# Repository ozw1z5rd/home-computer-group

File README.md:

# Home-Computer-Group

* ARM_ASM contains assembler programs you can run on Raspberry PI / PICO PI
* The C64 folder contains the source code as shown in the Home Computer Group e-magazine.
* KiCAD folder contains hardware projects for KiCAD
* Logicsim and LogiSimEvoluation are loaded with the circuits as shown in the Home Computer Group e-magazine.

Join us [Facebook group](https://fb.com/groups/home.computer) 

Visit us [Home Computer Group Website](https://homecomputer.group) 

Have fun with your Home Computer!

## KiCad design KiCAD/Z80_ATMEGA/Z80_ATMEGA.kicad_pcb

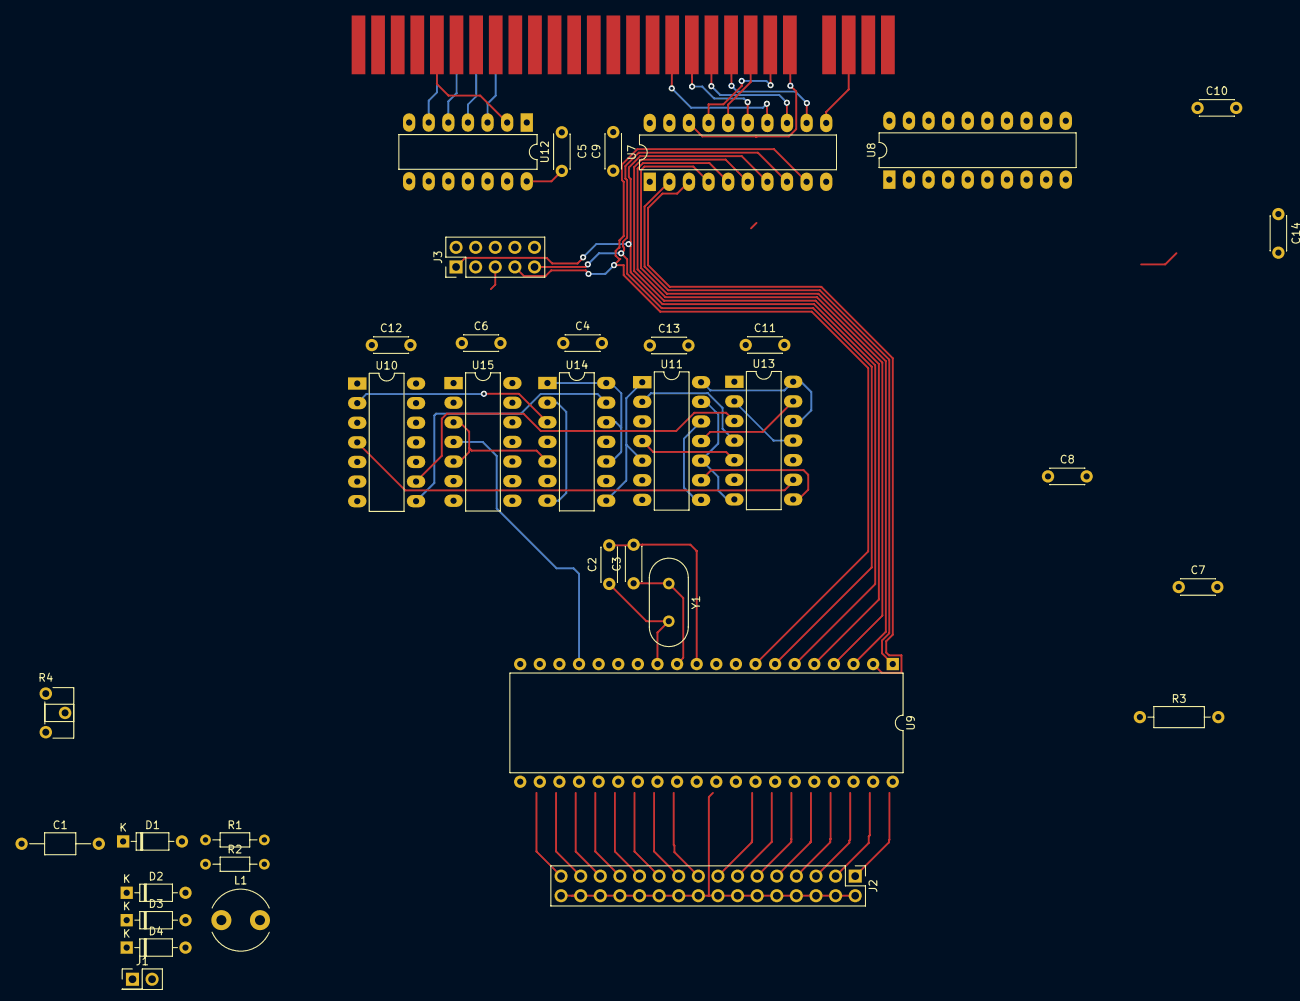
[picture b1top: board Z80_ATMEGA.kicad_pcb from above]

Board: 2 copper layers, 37 parts (0 on the bottom side), 76 nets.

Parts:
C1: C; C_Axial_L3.8mm_D2.6mm_P10.00mm_Horizontal
C2, C3, C4: 22pF; C_Disc_D4.3mm_W1.9mm_P5.00mm
C5, C6: 100nF; C_Disc_D4.3mm_W1.9mm_P5.00mm
C7, C8, C9, C10, C11, C12, C13, C14: 10pF; C_Disc_D4.3mm_W1.9mm_P5.00mm
CN1: ZXSPECTRUM_Expansion_Port; ZXSPECTRUM Expansion Port
D1, D2, D3, D4: 1N4148; D_DO-35_SOD27_P7.62mm_Horizontal
J1: Conn_01x02_Pin; PinHeader_2x01_P2.54mm_Vertical
J2: Conn_02x16_Odd_Even; PinHeader_2x16_P2.54mm_Vertical
J3: Conn_02x05_Odd_Even; PinHeader_2x05_P2.54mm_Vertical
L1: 100uH; L_Radial_D7.8mm_P5.00mm_Fastron_07HCP
R1, R2: R; R_Axial_DIN0204_L3.6mm_D1.6mm_P7.62mm_Horizontal
R3: 10K; R_Axial_DIN0207_L6.3mm_D2.5mm_P10.16mm_Horizontal
R4: 100K; Potentiometer_ACP_CA6-H2,5_Horizontal
U7: 74HC245; DIP-20_W7.62mm_LongPads
U8: 74HC244; DIP-20_W7.62mm_LongPads
U9: ATmega16L-8P; DIP-40_W15.24mm
U10: 74HC04; DIP-14_W7.62mm_LongPads
U11: 74LS32; DIP-14_W7.62mm_LongPads
U12: 74LS30; DIP-14_W7.62mm_LongPads
U13: 74HC00; DIP-14_W7.62mm_LongPads
U14: 74HC74; DIP-14_W7.62mm_LongPads
U15: 74HC02; DIP-14_W7.62mm_LongPads
Y1: 8Mhz; Crystal_HC49-4H_Vertical

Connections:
/A0: CN1.B9 (A0), U12.11
/A1: CN1.B10 (A1), U9.18 (PD4)
/A2: CN1.B11 (A2), U9.19 (PD5)
/A3: CN1.B12 (A3), U9.20 (PD6)
/A4: CN1.B24 (A4), U12.6
/A5: CN1.B23 (A5), U12.5
/A6: CN1.B22 (A6), U12.4
/A7: CN1.B21 (A7), U12.3
/ATM0: J2.1, U9.40 (PA0)
/ATM1: J2.3, U9.39 (PA1)
/ATM2: J2.5, U9.38 (PA2)
/ATM3: J2.7, U9.37 (PA3)
/ATM4: J2.9, U9.36 (PA4)
/ATM5: J2.11, U9.35 (PA5)
/ATM6: J2.13, U9.34 (PA6)
/ATM7: J2.15, U9.33 (PA7)
/ATM8: J2.17, U9.29 (PC7)
/ATM9: J2.19, U9.28 (PC6)
/ATM10: J2.21, U9.27 (PC5)
/ATM11: J2.23, U9.26 (PC4)
/ATM12: J2.25, U9.25 (PC3)
/ATM13: J2.27, U9.24 (PC2)
/ATM14: J2.29, U9.23 (PC1)
/ATM15: J2.31, U9.22 (PC0)
/D0: CN1.A6 (D0), U7.18 (B0), U8.18 (1Y0)
/D1: CN1.A7 (D1), U7.17 (B1), U8.16 (1Y1)
/D2: CN1.A8 (D2), U7.16 (B2), U8.14 (1Y2)
/D3: CN1.A11 (D3), U7.15 (B3), U8.12 (1Y3)
/D4: CN1.A12 (D4), U7.14 (B4), U8.3 (2Y0)
/D5: CN1.A10 (D5), U7.13 (B5), U8.5 (2Y1)
/D6: CN1.A9 (D6), U7.12 (B6), U8.7 (2Y2)
/D7: CN1.A3 (D7), U7.11 (B7), U8.9 (2Y3)
/DATA0: U7.2 (A0), U9.1 (PB0)
/DATA1: U7.3 (A1), U9.2 (PB1)
/DATA2: U7.4 (A2), U9.3 (PB2)
/DATA3: U7.5 (A3), U9.4 (PB3)
/DATA4: U7.6 (A4), U9.5 (PB4)
/DATA5: J3.1, U7.7 (A5), U9.6 (PB5)
/DATA6: J3.9, U7.8 (A6), U9.7 (PB6)
/DATA7: J3.7, U7.9 (A7), U9.8 (PB7)
/INT: D2.1 (K), U11.1, U11.5, U14.8 (~Q)
/IORQ: CN1.A17 (~IOREQ), U10.13
/LOGIC/D1: U8.4 (1A1), U11.3
/LOGIC/D2: U8.6 (1A2), U11.6
/LOGIC/INT0: U9.16 (PD2), U15.1
/LOGIC/INT1: U9.17 (PD3), U15.4
/LOGIC/Z80_ISR0: U9.15 (PD1), U11.2, U13.4
/LOGIC/Z80_ISR1: U9.14 (PD0), U11.4, U13.5
/LOGIC/~DISABLE_Z80_WAIT: D1.2 (A), U9.21 (PD7), U14.4 (~S)
/LOGIC/~OE2: U8.1 (1OE), U8.19 (2OE), U11.9, U13.1, U13.8
/LOGIC/~OE: U7.19 (CE), U10.1, U12.8
/M1: CN1.A24 (~M1), U10.3, U12.2
/R: CN1.A18 (~RD), U7.1 (A->B), U15.2
/W: CN1.A19 (~WR), U15.6
/WAIT: CN1.A21 (~WAIT), U14.5 (Q), U15.3, U15.5
GND: C1.2, C2.2, C3.2, C4.1, C5.2, C6.2, C7.2, C8.2, C9.2, C10.2, C11.2, C12.2, C13.2, C14.2, CN1.B6 (GND), CN1.B7 (GND), CN1.B14 (GND), J1.2, J2.2, J2.4, J2.6, J2.8, J2.10, J2.12, J2.14, J2.16, J2.18, J2.20, J2.22, J2.24, J2.26, J2.28, J2.30, J2.32, J3.3, J3.8, J3.10, U7.10 (GND), U8.10 (GND), U9.11 (GND), U9.31 (GND), U10.7 (GND), U11.7 (GND), U11.10, U11.13, U12.7 (GND), U13.7 (GND), U14.2 (D), U14.7 (GND), U15.7 (GND)
unnamed: C1.1, R1.1, R2.2
unnamed: CN1.A13 (~INT), D2.2 (A)
unnamed: D1.1 (K), R2.1
unnamed: C4.2, D3.2 (A), D4.2 (A), R3.2, U9.9 (~RESET)
unnamed: J1.1, R4.1
unnamed: R4.2, U9.32 (AREF)
unnamed: L1.1, U9.30 (AVCC)
unnamed: C2.1, U9.13 (XTAL1), Y1.2
unnamed: C3.1, U9.12 (XTAL2), Y1.1
unnamed: U10.4, U13.9
unnamed: U10.9, U13.3
unnamed: U10.12, U12.1, U13.10
unnamed: U11.11, U13.13
unnamed: U11.8, U11.12
unnamed: U13.2, U13.11
unnamed: U10.2, U14.3 (C)
unnamed: U13.6, U14.11 (C)
unnamed: U10.8, U14.13 (~R)
VCC: C5.1, C6.1, C7.1, C8.1, C9.1, C10.1, C11.1, C12.1, C13.1, C14.1, CN1.B3 (+5V), D3.1 (K), J3.2, L1.2, R1.2, R3.1, U7.20 (VCC), U8.2 (1A0), U8.8 (1A3), U8.11 (2A3), U8.13 (2A2), U8.15 (2A1), U8.17 (2A0), U8.20 (VCC), U9.10 (VCC), U10.14 (VCC), U11.14 (VCC), U12.14 (VCC), U13.12, U13.14 (VCC), U14.1 (~R), U14.10 (~S), U14.12 (D), U14.14 (VCC), U15.14 (VCC)
~ATMEGA_RESET: D4.1 (K), J3.5

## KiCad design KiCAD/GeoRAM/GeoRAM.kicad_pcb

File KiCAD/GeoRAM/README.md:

This repository contains the full project of the GeoRAM clone. You can import it with no issue but before doing that, you have to import the Commodore64 Edge connector from the Library folder. 

For help, join the facebook group: [Home Computer Group](https://fb.com/groups/home.computer). 

If you are looking for Commodore 64 programs GeoRAM capable, visit the [website](https://homecomputer.group).

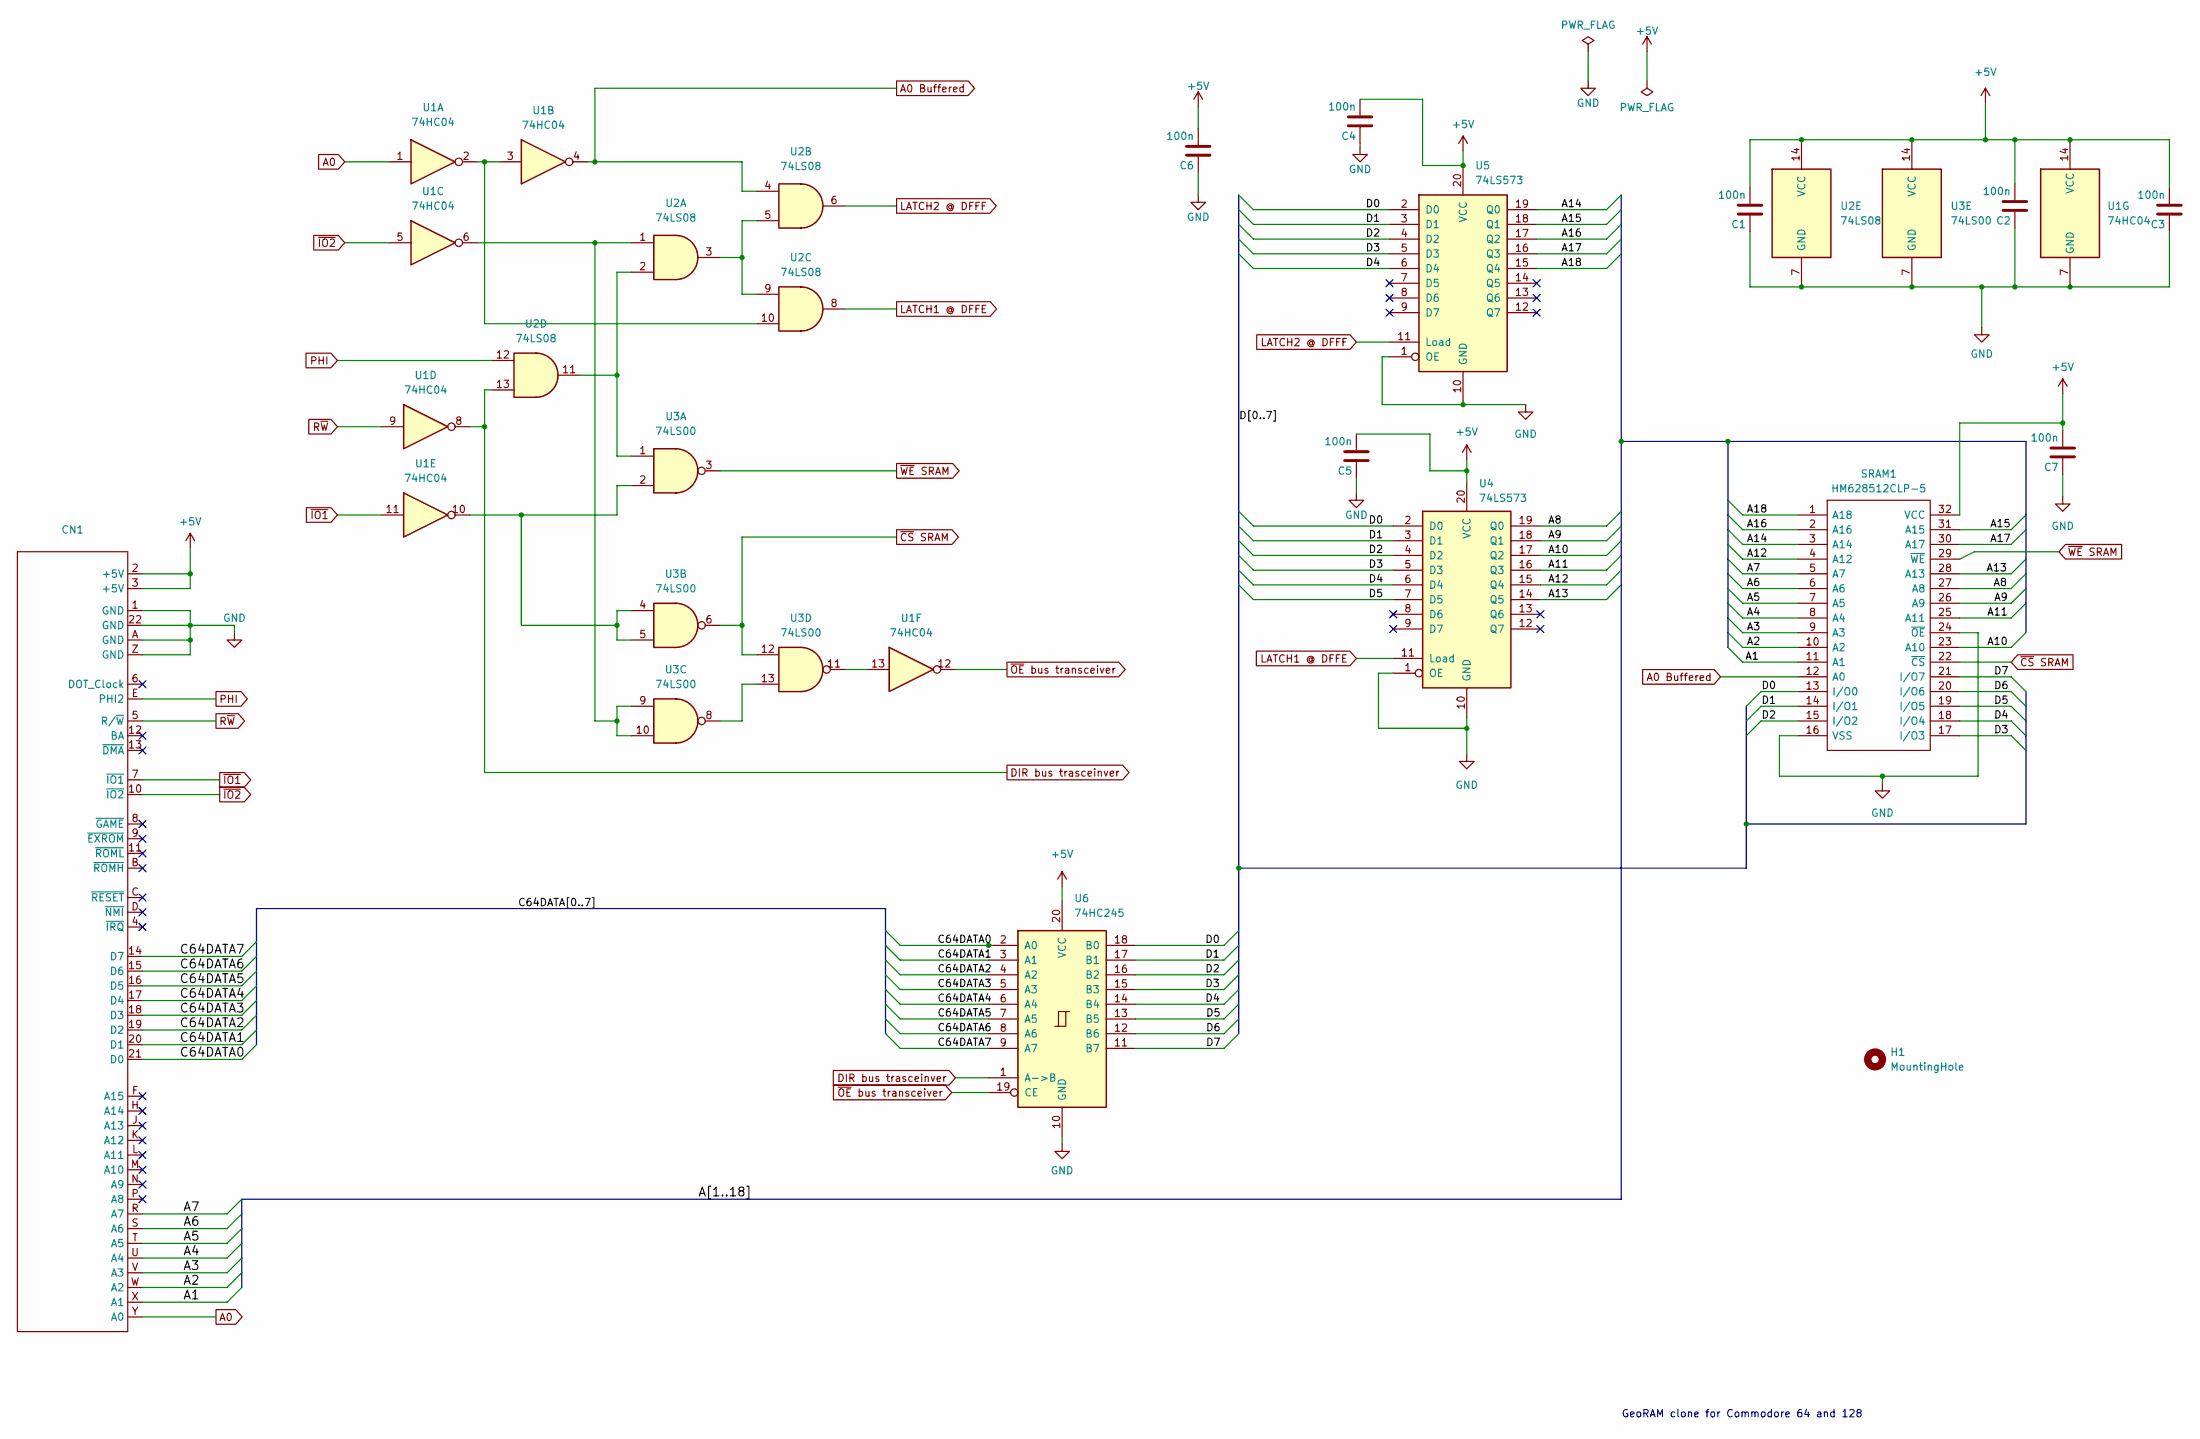
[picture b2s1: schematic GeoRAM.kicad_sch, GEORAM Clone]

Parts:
C1, C2, C3, C4, C5, C6, C7: 100n; C_Disc_D3.0mm_W1.6mm_P2.50mm
CN1: C64 Cartridge Expansion
H1: MountingHole; MountingHole_5.5mm
SRAM1: HM628512CLP-5; DIP-32_W15.24mm; Manufacturer_Part_Number HM628512CLP-5
U1: 74HC04; DIP-14_W7.62mm
U2: 74LS08; DIP-14_W7.62mm
U3: 74LS00; DIP-14_W7.62mm
U4, U5: 74LS573; DIP-20_W7.62mm
U6: 74HC245; DIP-20_W7.62mm

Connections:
+5V: C1.2, C2.2, C3.2, C4.2, C5.2, C6.2, C7.2, CN1.2 (+5V), CN1.3 (+5V), SRAM1.32 (VCC), U1.14 (VCC), U2.14 (VCC), U3.14 (VCC), U4.20 (VCC), U5.20 (VCC), U6.20 (VCC)
/A1: CN1.X (A1), SRAM1.11 (A1)
/A2: CN1.W (A2), SRAM1.10 (A2)
/A3: CN1.V (A3), SRAM1.9 (A3)
/A4: CN1.U (A4), SRAM1.8 (A4)
/A5: CN1.T (A5), SRAM1.7 (A5)
/A6: CN1.S (A6), SRAM1.6 (A6)
/A7: CN1.R (A7), SRAM1.5 (A7)
/A8: SRAM1.27 (A8), U4.19 (Q0)
/A9: SRAM1.26 (A9), U4.18 (Q1)
/A10: SRAM1.23 (A10), U4.17 (Q2)
/A11: SRAM1.25 (A11), U4.16 (Q3)
/A12: SRAM1.4 (A12), U4.15 (Q4)
/A13: SRAM1.28 (A13), U4.14 (Q5)
/A14: SRAM1.3 (A14), U5.19 (Q0)
/A15: SRAM1.31 (A15), U5.18 (Q1)
/A16: SRAM1.2 (A16), U5.17 (Q2)
/A17: SRAM1.30 (A17), U5.16 (Q3)
/A18: SRAM1.1 (A18), U5.15 (Q4)
/C64DATA0: CN1.21 (D0), U6.2 (A0)
/C64DATA1: CN1.20 (D1), U6.3 (A1)
/C64DATA2: CN1.19 (D2), U6.4 (A2)
/C64DATA3: CN1.18 (D3), U6.5 (A3)
/C64DATA4: CN1.17 (D4), U6.6 (A4)
/C64DATA5: CN1.16 (D5), U6.7 (A5)
/C64DATA6: CN1.15 (D6), U6.8 (A6)
/C64DATA7: CN1.14 (D7), U6.9 (A7)
/D0: SRAM1.13 (I/O0), U4.2 (D0), U5.2 (D0), U6.18 (B0)
/D1: SRAM1.14 (I/O1), U4.3 (D1), U5.3 (D1), U6.17 (B1)
/D2: SRAM1.15 (I/O2), U4.4 (D2), U5.4 (D2), U6.16 (B2)
/D3: SRAM1.17 (I/O3), U4.5 (D3), U5.5 (D3), U6.15 (B3)
/D4: SRAM1.18 (I/O4), U4.6 (D4), U5.6 (D4), U6.14 (B4)
/D5: SRAM1.19 (I/O5), U4.7 (D5), U6.13 (B5)
/D6: SRAM1.20 (I/O6), U6.12 (B6)
/D7: SRAM1.21 (I/O7), U6.11 (B7)
A0: CN1.Y (A0), U1.1
A0 Buffered: SRAM1.12 (A0), U1.4, U2.4
DIR bus trasceinver: U1.8, U2.13, U6.1 (A->B)
GND: C1.1, C2.1, C3.1, C4.1, C5.1, C6.1, C7.1, CN1.1 (GND), CN1.22 (GND), CN1.A (GND), CN1.Z (GND), SRAM1.16 (VSS), SRAM1.24 (~OE), U1.7 (GND), U2.7 (GND), U3.7 (GND), U4.1 (OE), U4.10 (GND), U5.1 (OE), U5.10 (GND), U6.10 (GND)
LATCH1 @ DFFE: U2.8, U4.11 (Load)
LATCH2 @ DFFF: U2.6, U5.11 (Load)
unnamed: U1.2, U1.3, U2.10
unnamed: U1.6, U2.1, U3.9, U3.10
unnamed: U1.10, U3.2, U3.4, U3.5
unnamed: U1.13, U3.11
unnamed: U2.3, U2.5, U2.9
unnamed: U2.2, U2.11, U3.1
unnamed: U3.8, U3.13
PHI: CN1.E (PHI2), U2.12
R~W: CN1.5 (R/~W), U1.9
~CS SRAM: SRAM1.22 (~CS), U3.6, U3.12
~IO1: CN1.7 (~IO1), U1.11
~IO2: CN1.10 (~IO2), U1.5
~OE bus transceiver: U1.12, U6.19 (CE)
~WE SRAM: SRAM1.29 (~WE), U3.3

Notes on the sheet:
GeoRAM clone for Commodore 64 and 128

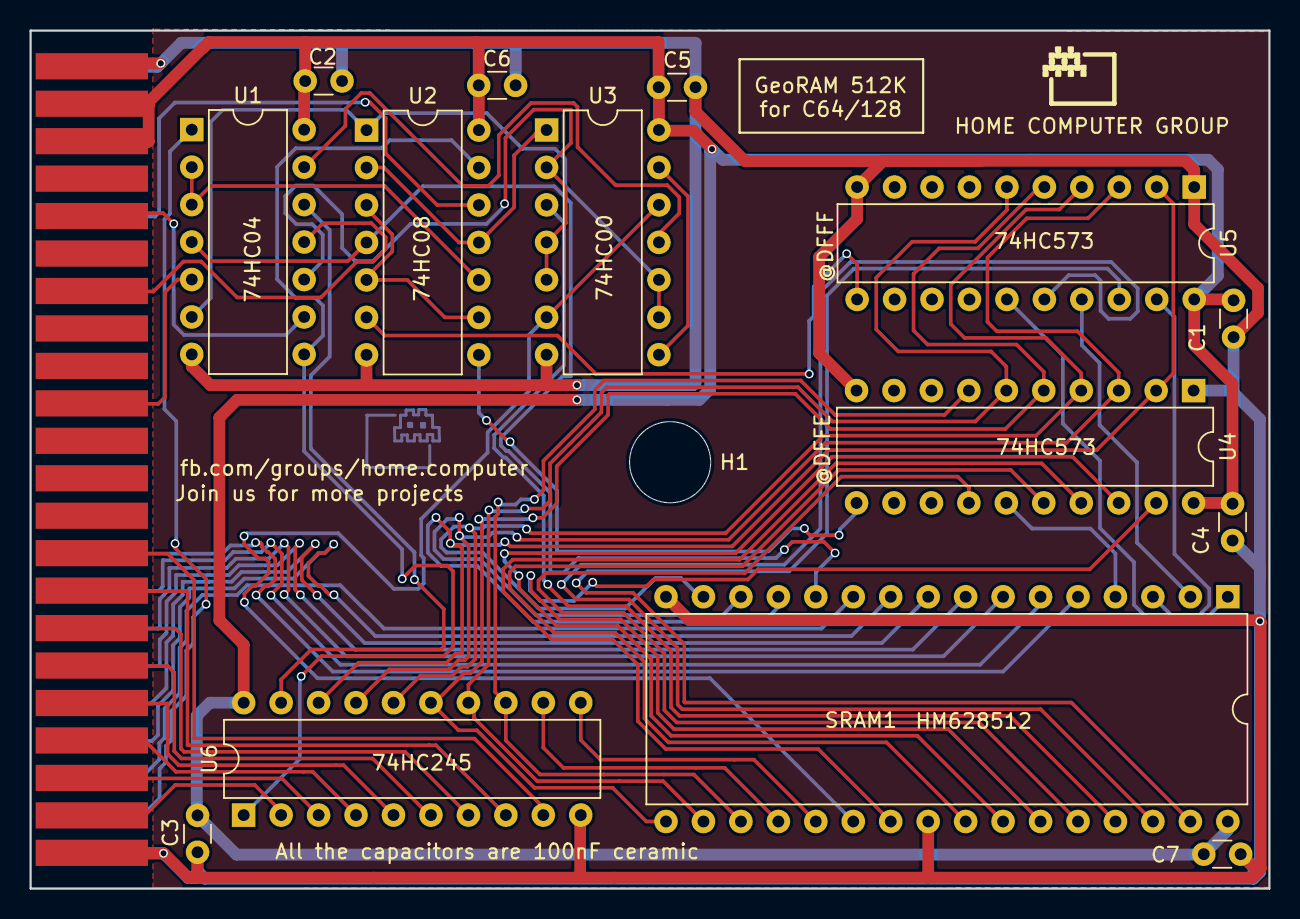
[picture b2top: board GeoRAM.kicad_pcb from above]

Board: 2 copper layers, 84.0 x 58.2 mm, 16 parts (0 on the bottom side), 55 nets.

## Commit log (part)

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2022-04-20 Digital locker
2022-09-06 GeoRAM clone glue logic simulation
2022-09-06 Add schematic image
2023-01-07 OpenC64Cart_modified for GEORAM clone
2023-01-07 Added screenshots
2023-01-09 Fixed some problems on the PCB that prevent the correct parsing on PCBWay
2023-02-02 Version 2.0, fixed several issues with the original design
2023-05-21 ATMEGA-Z80
2024-01-07 New folder layout + 4bit adder
2024-01-14 GeoRAM programming in CC65
2024-01-20 Edge Connector Library
2024-01-21 Source code Issue #17
2024-02-25 Source code Issue #18, not yet completed
2024-03-03 Source code Issue #18, completed
2024-03-17 HCG18 + layout change for HCG17
2024-05-01 Updated and fixed Commodore and Sinclair edge connectors
2024-05-01 Add the GeoRAM project for KiCAD 8.0.2
2024-05-01 Add logo
2024-05-03 Apple II slot edge connector
2024-05-03 Added AppleII EEPROM
2024-05-03 Added Z80 ATMEL interfacing
2024-05-03 Prework HCG19
2024-05-06 Adding something interesting
2024-05-19 still some bugs to be fixed
2024-05-19 Bug fixed
2024-05-19 minor changes
2024-05-19 Fix a little issue
2024-06-17 Floating point/2
2024-06-17 add minmax
2024-07-17 HCG20, 6502 & AY-3-891x
2024-08-26 NEXT project files
2024-09-08 Floating point exceptions
2024-09-12 github as shared folder... pushing incomplete files
2024-09-17 Small changes
2024-09-17 +config
2024-11-19 HCG20 Overlay with GeoRAM demo
2024-11-19 Remove unused files
2024-11-19 Change disk name

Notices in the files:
KiCAD/GeoRAM/GeoRAM.kicad_pcb:
Creative Commons
CC BY-ND 4.0
